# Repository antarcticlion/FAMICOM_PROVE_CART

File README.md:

# FAMICOM_PROVE_CART
Famicom 60pin cartridge Probing Board. (For Logic analyzer / Oscilloscope / Multimeter / etc.)

## 概要

ファミコンの60ピンカートリッジバスの信号をモニターするための基板です。  
プロジェクトにはKiCad PCB 5.0用のプロジェクトファイルとガーバーが含まれます。

## 作り方

ボードを基板製造業者に発注する場合、1.2mm厚で注文してください。  
基板上部に2.54mmピッチ60ピンのカードエッジソケットを半田付けします。  
ボード中央のスルーホールは、使用する測定機材にあわせて、ピンヘッダやテストピンを半田付けしてください。

## 使い方
ファミコン本体とカートリッジ間に設置します。  
「FRONT SIDE」と書かれた方が正面です。  
正面から見て左下が1番ピン、左上が2番ピン、右下が59番ピン、右上が60番ピンです。

標準より重心が高くなりますので、ディスクシステム用RAMカートリッジ等の大きめカートリッジは不安定になりますので注意してください。

（このボードを使用してキャプチャした信号のサンプル：PRG-ROM側の制御線、アドレス線上位）

## Note
ネットリストは改変時に一括で再生成するので削除しました。

## Lastest Gerber

Rev 0.1 fix 1
https://github.com/antarcticlion/FAMICOM_PROVE_CART/blob/master/gerber_FAMICOM_PROVE_CART01B.zip

## Changes Log  
| Revision | Date | Description |
|:---|:---|:---|
|0.1 fix 1 |2019/02/26 |Typo fix |
|0.1 |2019/02/26 |First Release |

## ライセンス
クリエイティブコモンズ　表示 - 継承 4.0 国際 (CC BY-SA 4.0)

https://creativecommons.org/licenses/by-sa/4.0/  
https://creativecommons.org/licenses/by-sa/4.0/legalcode

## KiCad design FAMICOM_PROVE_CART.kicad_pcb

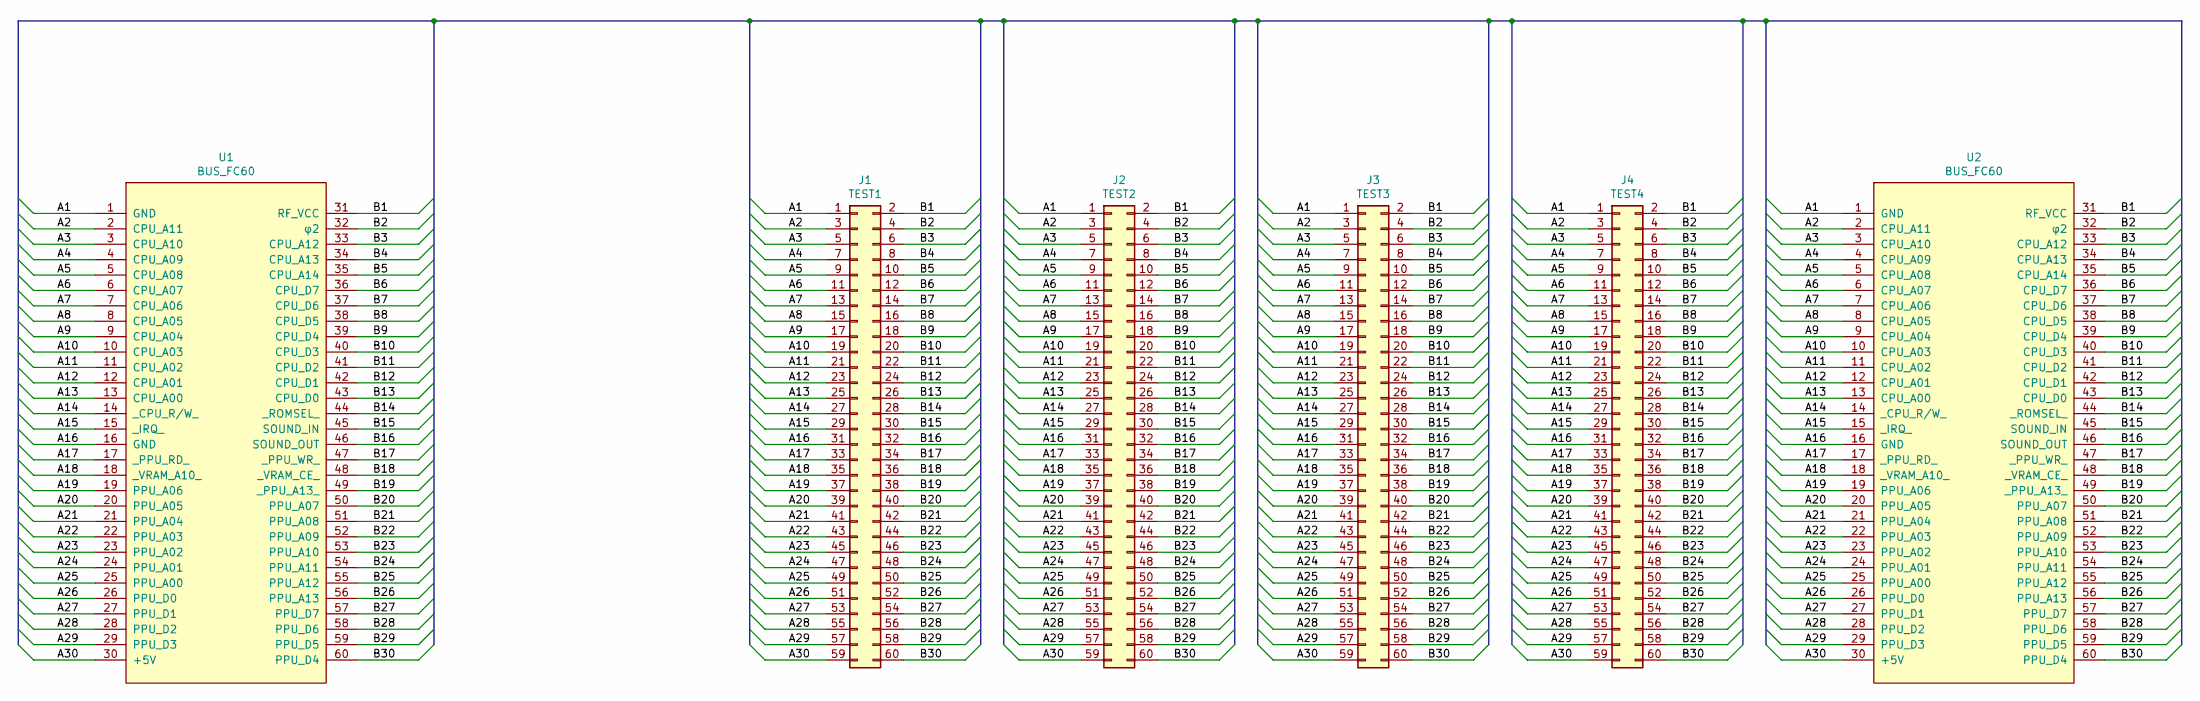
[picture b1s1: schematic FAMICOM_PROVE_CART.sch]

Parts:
J1: TEST1; Pin_Header_Straight_2x30_Pitch2.54mm
J2: TEST2; Pin_Header_Straight_2x30_Pitch2.54mm
J3: TEST3; Pin_Header_Straight_2x30_Pitch2.54mm
J4: TEST4; Pin_Header_Straight_2x30_Pitch2.54mm
U1, U2: BUS_FC60; BUS_FC_60

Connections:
/A1: J1.1, J2.1, J3.1, J4.1, U1.1 (GND), U2.1 (GND); also elsewhere on the board
/A2: J1.3, J2.3, J3.3, J4.3, U1.2 (CPU_A11), U2.2 (CPU_A11)
/A3: J1.5, J2.5, J3.5, J4.5, U1.3 (CPU_A10), U2.3 (CPU_A10)
/A4: J1.7, J2.7, J3.7, J4.7, U1.4 (CPU_A09), U2.4 (CPU_A09)
/A5: J1.9, J2.9, J3.9, J4.9, U1.5 (CPU_A08), U2.5 (CPU_A08)
/A6: J1.11, J2.11, J3.11, J4.11, U1.6 (CPU_A07), U2.6 (CPU_A07)
/A7: J1.13, J2.13, J3.13, J4.13, U1.7 (CPU_A06), U2.7 (CPU_A06)
/A8: J1.15, J2.15, J3.15, J4.15, U1.8 (CPU_A05), U2.8 (CPU_A05)
/A9: J1.17, J2.17, J3.17, J4.17, U1.9 (CPU_A04), U2.9 (CPU_A04)
/A10: J1.19, J2.19, J3.19, J4.19, U1.10 (CPU_A03), U2.10 (CPU_A03)
/A11: J1.21, J2.21, J3.21, J4.21, U1.11 (CPU_A02), U2.11 (CPU_A02)
/A12: J1.23, J2.23, J3.23, J4.23, U1.12 (CPU_A01), U2.12 (CPU_A01)
/A13: J1.25, J2.25, J3.25, J4.25, U1.13 (CPU_A00), U2.13 (CPU_A00)
/A14: J1.27, J2.27, J3.27, J4.27, U1.14 (_CPU_R/W_), U2.14 (_CPU_R/W_)
/A15: J1.29, J2.29, J3.29, J4.29, U1.15 (_IRQ_), U2.15 (_IRQ_)
/A16: J1.31, J2.31, J3.31, J4.31, U1.16 (GND), U2.16 (GND)
/A17: J1.33, J2.33, J3.33, J4.33, U1.17 (_PPU_RD_), U2.17 (_PPU_RD_)
/A18: J1.35, J2.35, J3.35, J4.35, U1.18 (_VRAM_A10_), U2.18 (_VRAM_A10_)
/A19: J1.37, J2.37, J3.37, J4.37, U1.19 (PPU_A06), U2.19 (PPU_A06)
/A20: J1.39, J2.39, J3.39, J4.39, U1.20 (PPU_A05), U2.20 (PPU_A05)
/A21: J1.41, J2.41, J3.41, J4.41, U1.21 (PPU_A04), U2.21 (PPU_A04)
/A22: J1.43, J2.43, J3.43, J4.43, U1.22 (PPU_A03), U2.22 (PPU_A03)
/A23: J1.45, J2.45, J3.45, J4.45, U1.23 (PPU_A02), U2.23 (PPU_A02)
/A24: J1.47, J2.47, J3.47, J4.47, U1.24 (PPU_A01), U2.24 (PPU_A01)
/A25: J1.49, J2.49, J3.49, J4.49, U1.25 (PPU_A00), U2.25 (PPU_A00)
/A26: J1.51, J2.51, J3.51, J4.51, U1.26 (PPU_D0), U2.26 (PPU_D0)
/A27: J1.53, J2.53, J3.53, J4.53, U1.27 (PPU_D1), U2.27 (PPU_D1)
/A28: J1.55, J2.55, J3.55, J4.55, U1.28 (PPU_D2), U2.28 (PPU_D2)
/A29: J1.57, J2.57, J3.57, J4.57, U1.29 (PPU_D3), U2.29 (PPU_D3)
/A30: J1.59, J2.59, J3.59, J4.59, U1.30 (+5V), U2.30 (+5V)
/B1: J1.2, J2.2, J3.2, J4.2, U1.31 (RF_VCC), U2.31 (RF_VCC); also elsewhere on the board
/B2: J1.4, J2.4, J3.4, J4.4, U1.32 (φ2), U2.32 (φ2)
/B3: J1.6, J2.6, J3.6, J4.6, U1.33 (CPU_A12), U2.33 (CPU_A12)
/B4: J1.8, J2.8, J3.8, J4.8, U1.34 (CPU_A13), U2.34 (CPU_A13)
/B5: J1.10, J2.10, J3.10, J4.10, U1.35 (CPU_A14), U2.35 (CPU_A14)
/B6: J1.12, J2.12, J3.12, J4.12, U1.36 (CPU_D7), U2.36 (CPU_D7)
/B7: J1.14, J2.14, J3.14, J4.14, U1.37 (CPU_D6), U2.37 (CPU_D6)
/B8: J1.16, J2.16, J3.16, J4.16, U1.38 (CPU_D5), U2.38 (CPU_D5)
/B9: J1.18, J2.18, J3.18, J4.18, U1.39 (CPU_D4), U2.39 (CPU_D4)
/B10: J1.20, J2.20, J3.20, J4.20, U1.40 (CPU_D3), U2.40 (CPU_D3)
/B11: J1.22, J2.22, J3.22, J4.22, U1.41 (CPU_D2), U2.41 (CPU_D2)
/B12: J1.24, J2.24, J3.24, J4.24, U1.42 (CPU_D1), U2.42 (CPU_D1)
/B13: J1.26, J2.26, J3.26, J4.26, U1.43 (CPU_D0), U2.43 (CPU_D0)
/B14: J1.28, J2.28, J3.28, J4.28, U1.44 (_ROMSEL_), U2.44 (_ROMSEL_)
/B15: J1.30, J2.30, J3.30, J4.30, U1.45 (SOUND_IN), U2.45 (SOUND_IN)
/B16: J1.32, J2.32, J3.32, J4.32, U1.46 (SOUND_OUT), U2.46 (SOUND_OUT)
/B17: J1.34, J2.34, J3.34, J4.34, U1.47 (_PPU_WR_), U2.47 (_PPU_WR_)
/B18: J1.36, J2.36, J3.36, J4.36, U1.48 (_VRAM_CE_), U2.48 (_VRAM_CE_)
/B19: J1.38, J2.38, J3.38, J4.38, U1.49 (_PPU_A13_), U2.49 (_PPU_A13_)
/B20: J1.40, J2.40, J3.40, J4.40, U1.50 (PPU_A07), U2.50 (PPU_A07)
/B21: J1.42, J2.42, J3.42, J4.42, U1.51 (PPU_A08), U2.51 (PPU_A08)
/B22: J1.44, J2.44, J3.44, J4.44, U1.52 (PPU_A09), U2.52 (PPU_A09)
/B23: J1.46, J2.46, J3.46, J4.46, U1.53 (PPU_A10), U2.53 (PPU_A10)
/B24: J1.48, J2.48, J3.48, J4.48, U1.54 (PPU_A11), U2.54 (PPU_A11)
/B25: J1.50, J2.50, J3.50, J4.50, U1.55 (PPU_A12), U2.55 (PPU_A12)
/B26: J1.52, J2.52, J3.52, J4.52, U1.56 (PPU_A13), U2.56 (PPU_A13)
/B27: J1.54, J2.54, J3.54, J4.54, U1.57 (PPU_D7), U2.57 (PPU_D7)
/B28: J1.56, J2.56, J3.56, J4.56, U1.58 (PPU_D6), U2.58 (PPU_D6)
/B29: J1.58, J2.58, J3.58, J4.58, U1.59 (PPU_D5), U2.59 (PPU_D5)
/B30: J1.60, J2.60, J3.60, J4.60, U1.60 (PPU_D4), U2.60 (PPU_D4)

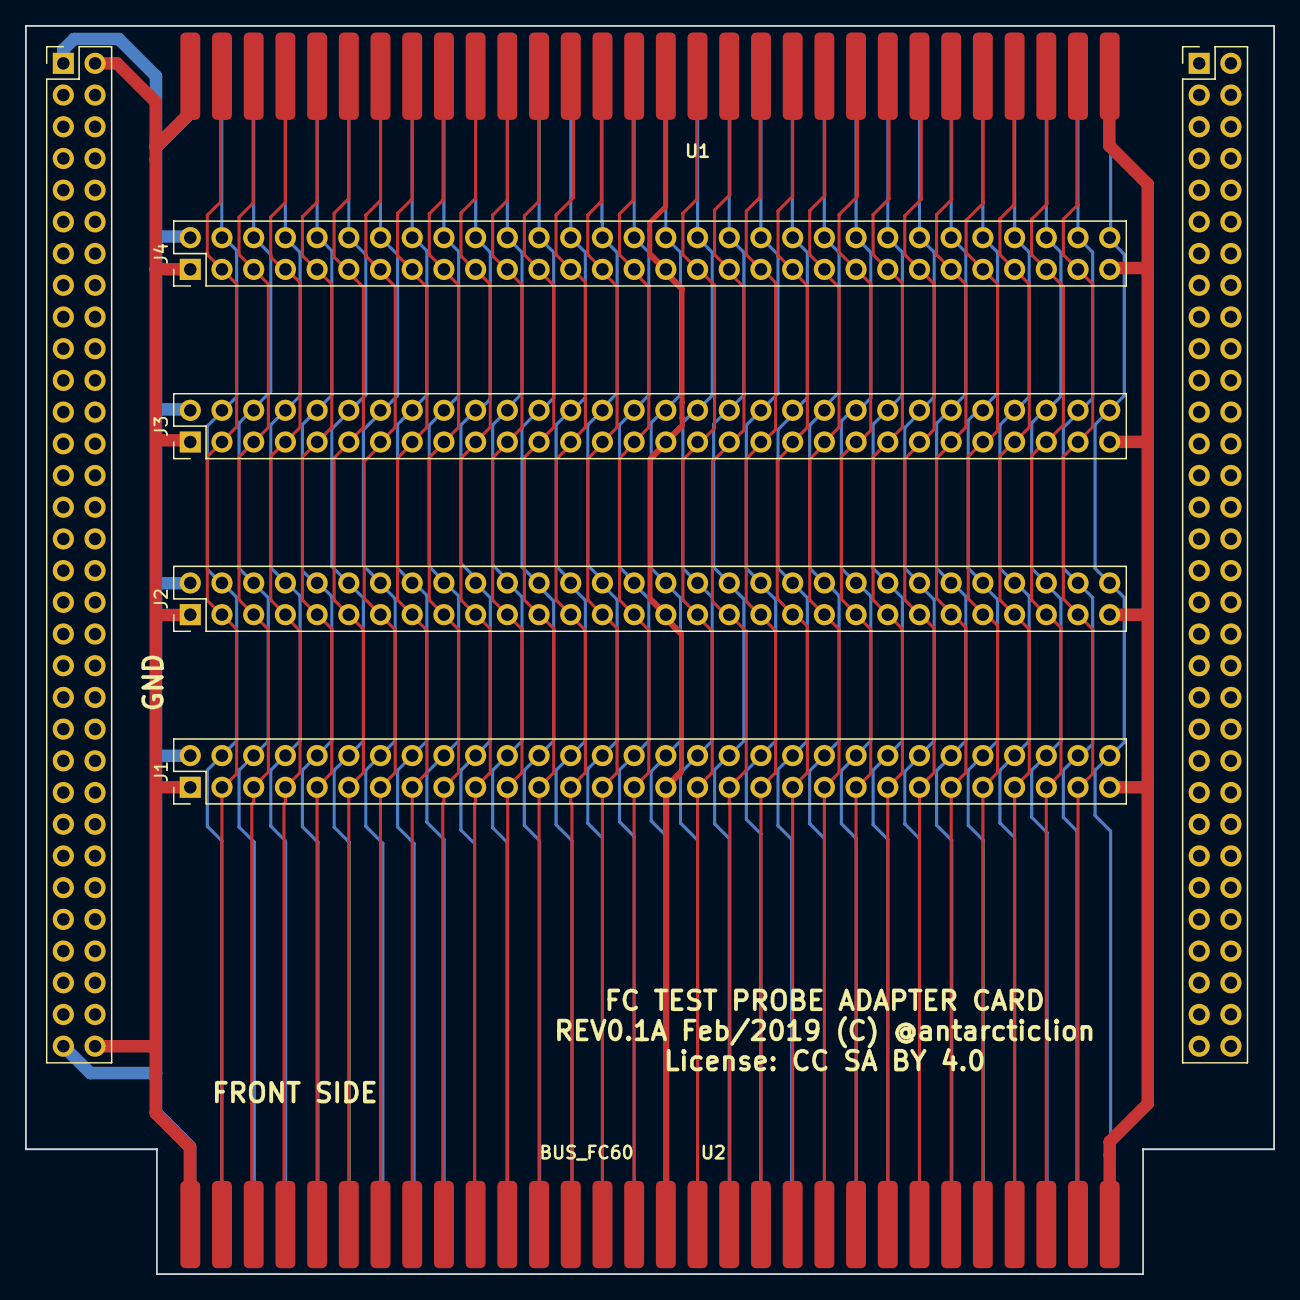
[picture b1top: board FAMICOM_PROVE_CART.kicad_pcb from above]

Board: 2 copper layers, 100.0 x 100.0 mm, 8 parts (0 on the bottom side), 60 nets.

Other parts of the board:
REF01, REF01#2: Pin_Header_Straight_2x32_Pitch2.54mm

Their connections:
/A1: REF01.2, REF01.64; also elsewhere on the board
/B1: REF01.1, REF01.63; also elsewhere on the board

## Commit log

2019-02-26 Initial upload.
2019-02-26 Rev 0.1 fix 1 gerber
2019-02-26 Rev 1.0 fix 1
    Typo fix
2019-03-03 delete

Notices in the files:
FAMICOM_PROVE_CART.kicad_pcb:
License: CC SA BY 4.0
